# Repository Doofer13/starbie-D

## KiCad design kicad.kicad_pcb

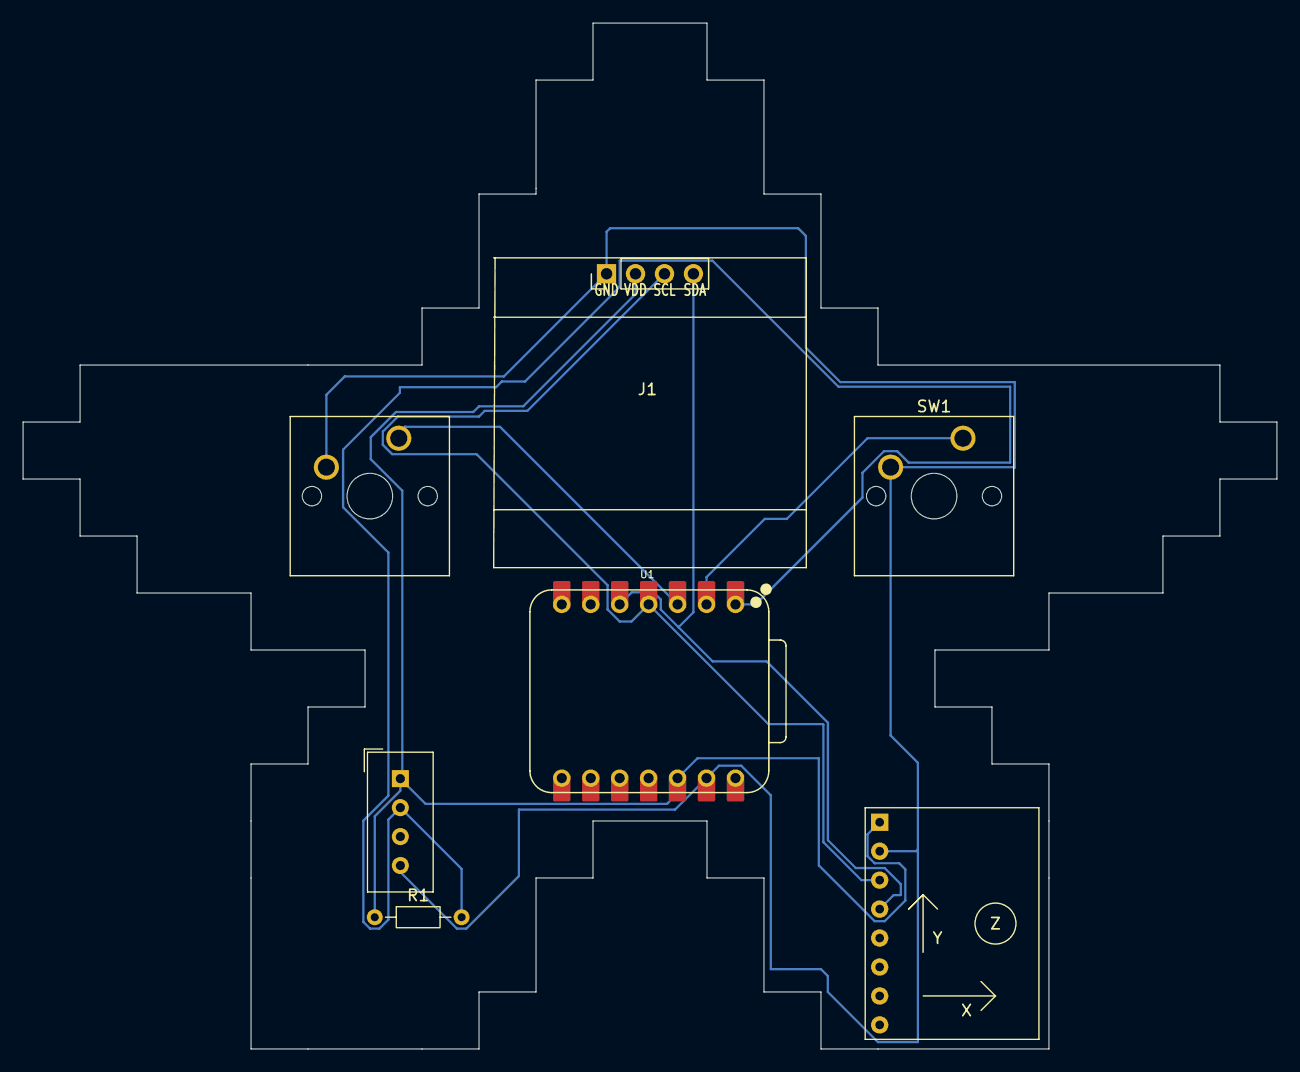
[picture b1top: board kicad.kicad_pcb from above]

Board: 2 copper layers, 110.0 x 90.0 mm, 7 parts (0 on the bottom side), 7 nets.

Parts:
J1: Conn_01x04_Pin; Display_128x64_096_I2C
J2: Conn_01x08_Pin; MPU6050_Module
R1: 10k; R_Axial_DIN0204_L3.6mm_D1.6mm_P7.62mm_Horizontal
SW1, SW2: SW_Push; SW_Cherry_MX_1.00u_PCB
U1: XIAO-ESP32-C3-SMD; XIAO-ESP32-C6-DIP
U2: DHT11; Aosong_DHT11_5.5x12.0_P2.54mm

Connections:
+3.3V: J1.2, J2.1, R1.1, U1.12 (3V3_OUT), U2.1 (VDD)
/DHT11 DATA: R1.2, U1.1 (D0), U2.2 (DATA)
/GPIO2: SW1.1, U1.2 (D1)
/GPIO3: SW2.1, U1.3 (D2)
/SCL: J1.3, J2.3, U1.4 (D3)
/SDA: J1.4, J2.4, U1.5 (D4)
GND: J1.1, J2.2, SW1.2, SW2.2, U1.13 (GND), U2.4 (GND)
